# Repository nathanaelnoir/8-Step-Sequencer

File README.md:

<h1>ℤ₈ Modulo-8 Sequencer</h1>

Modulo-8 Sequencer is an 8-step Eurorack sequencer with an onboard clock, external clock/reset inputs, and separate clock, gate, and CV outputs.

## Contents

- Overview
- Features
- Build & assembly notes
- Testing
- License & contributing

## Overview

This repository contains the KiCad 9 design files for Modulo-8 Sequencer, a straightforward 8-step CV/gate sequencer for Eurorack. Eight pots set the step voltages, the LEDs show the current position, and the module can run from its own clock or from an external pulse. `CLOCK OUT`, `GATE OUT`, `CV OUT`, and `RESET` are all available on the front panel.

## Features

- 8-step sequencer built around `CD4017BE` and `TL074`.
- Internal clock plus external `CLOCK IN`.
- Separate `CLOCK OUT`, `GATE OUT`, `CV OUT`, and `RESET` jacks.
- Eight 100 k step pots for setting the sequence voltage.
- Eight step LEDs for visual feedback.
- Rotary switch wired across `Count0` to `Count7` for loop-length / step-count selection.
- Standard Eurorack power: `+12 V / -12 V / GND` on a 10-pin header.
- Mixed build: SMD passives, diodes, and transistors, with through-hole panel hardware.

## Build & assembly notes

- Check pin-1 orientation on `U1` (`TL074`) and `U3` (`CD4017BE`) before soldering.
- Double-check the Eurorack power header orientation before applying power. Getting that wrong is an easy way to ruin the build.
- Panel hardware is not minimal: five 3.5 mm jacks, eight step pots, eight LEDs, several toggle switches, one rotary switch, and two trimmers (`RV1`, `RV2`).
- The power section includes ferrite beads and local decoupling on the rails. Populate it exactly as shown.
- This is a mixed SMD + THT build, so it makes sense to solder the low-profile SMD parts first and leave the panel hardware for last.

## Testing

1. Power the module from a current-limited Eurorack supply and verify `+12 V`, `-12 V`, and `GND` at the header and test points before patching anything.
2. Let the internal clock run and check that the step LEDs advance in order and that `CLOCK OUT` is pulsing.
3. Feed a known clock into `CLOCK IN` and confirm the sequence advances cleanly from the external source.
4. Trigger `RESET` and make sure the sequencer returns to step 1 or to the selected loop point.
5. Watch `GATE OUT` and `CV OUT` on a scope or with downstream modules and confirm that the outputs follow the programmed steps.

## License & contributing

No `LICENSE` file has been added to this repository yet. Until that changes, assume the design is shared for reference, not under an explicit open-source license.

If a license is added later, this section can be updated properly.

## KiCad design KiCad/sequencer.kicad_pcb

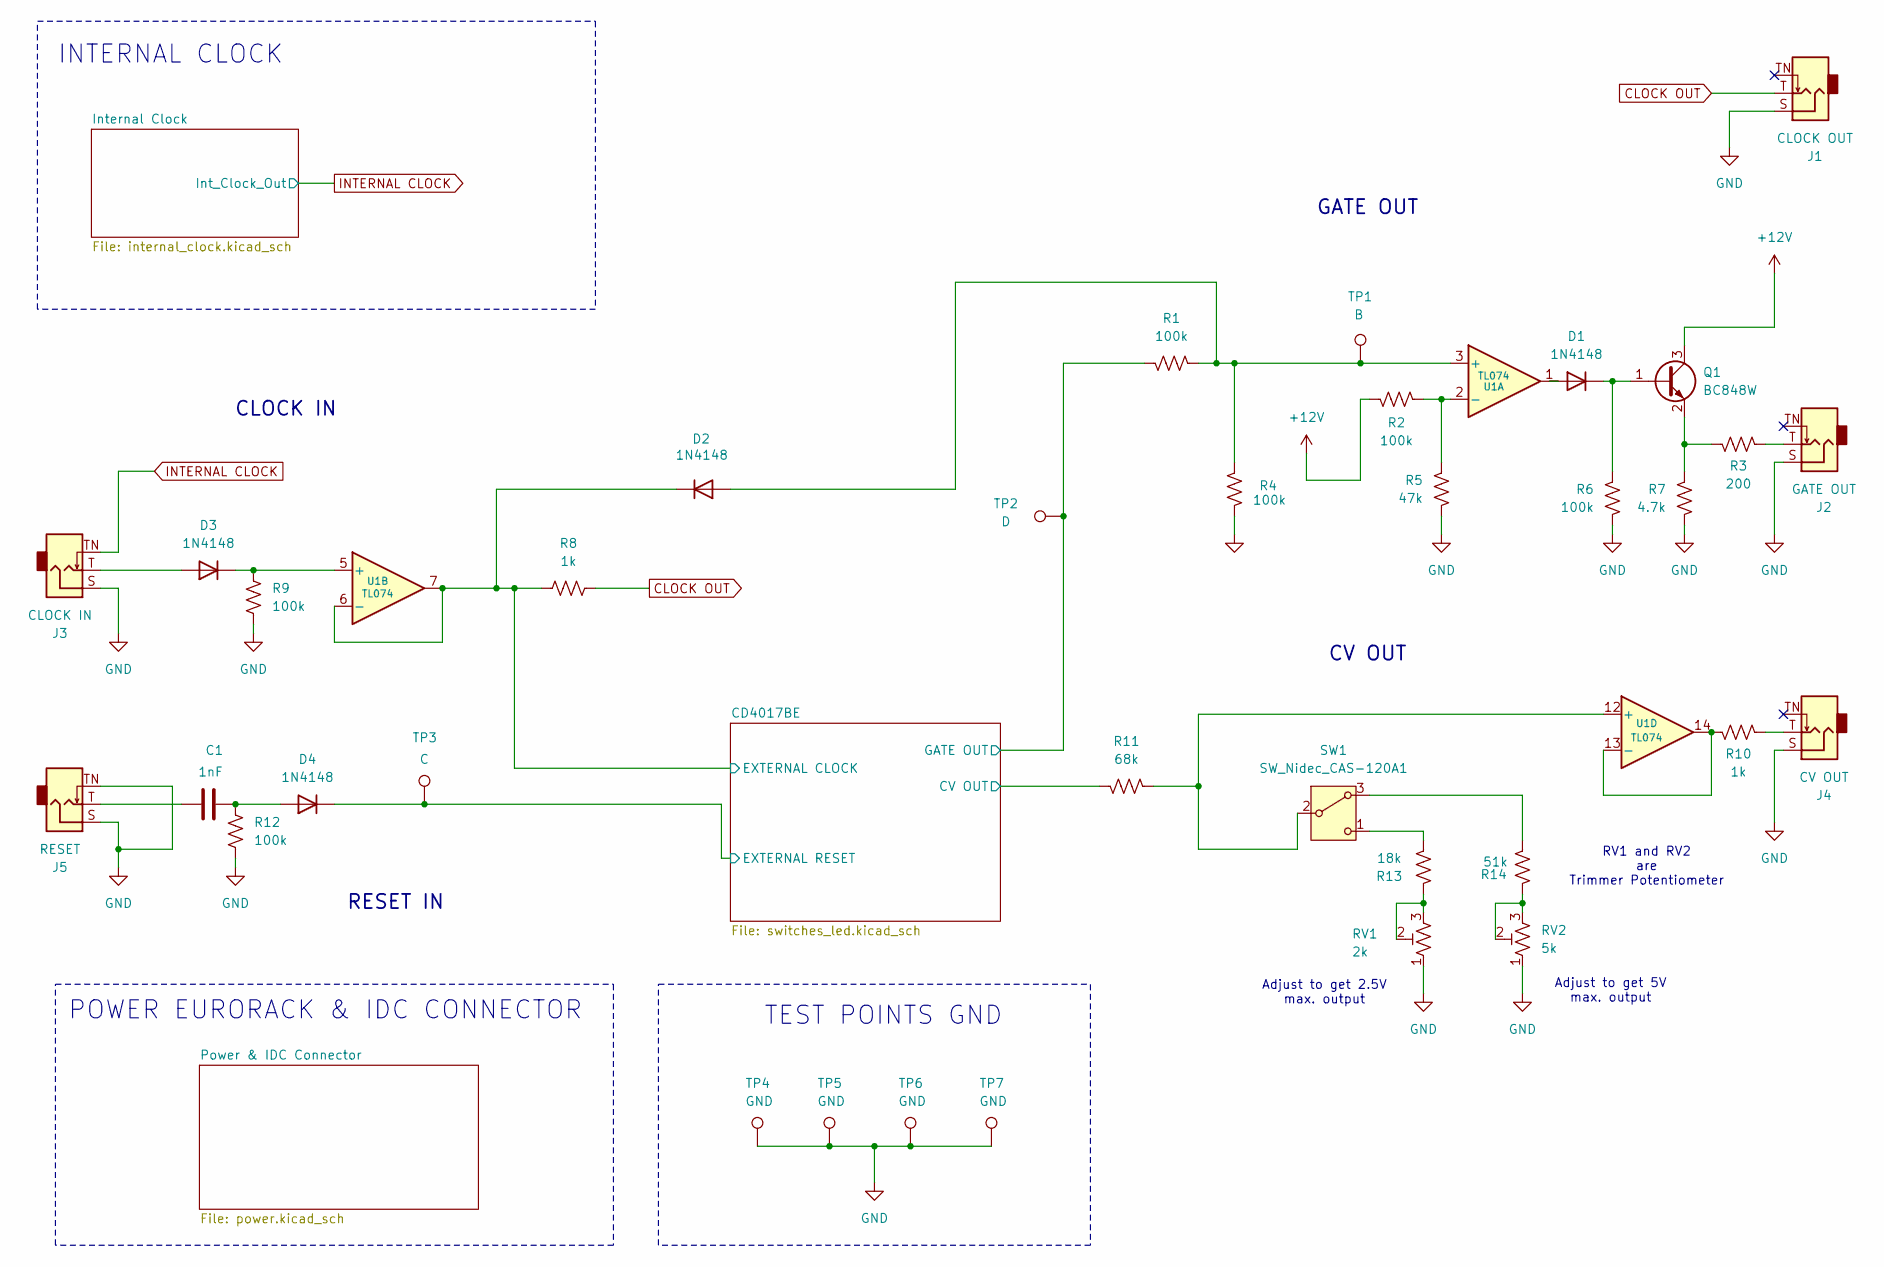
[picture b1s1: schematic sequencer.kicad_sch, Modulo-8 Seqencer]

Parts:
C1: 1nF; C_0805_2012Metric_Pad1.18x1.45mm_HandSolder
D1, D2, D3, D4: 1N4148; D_SOD-323_HandSoldering
J1: CLOCK OUT; Jack_3.5mm_QingPu_WQP-PJ398SM_Vertical
J2: GATE OUT; Jack_3.5mm_QingPu_WQP-PJ398SM_Vertical
J3: CLOCK IN; Jack_3.5mm_QingPu_WQP-PJ398SM_Vertical
J4: CV OUT; Jack_3.5mm_QingPu_WQP-PJ398SM_Vertical
J5: RESET; Jack_3.5mm_QingPu_WQP-PJ398SM_Vertical
Q1: BC848W; SOT-323_SC-70
R1, R2, R4, R6, R9, R12: 100k; R_0805_2012Metric_Pad1.20x1.40mm_HandSolder
R3: 200; R_0805_2012Metric_Pad1.20x1.40mm_HandSolder
R5: 47k; R_0805_2012Metric_Pad1.20x1.40mm_HandSolder
R7: 4.7k; R_0805_2012Metric_Pad1.20x1.40mm_HandSolder
R8, R10: 1k; R_0805_2012Metric_Pad1.20x1.40mm_HandSolder
R11: 68k; R_0805_2012Metric_Pad1.20x1.40mm_HandSolder
R13: 18k; R_0805_2012Metric_Pad1.20x1.40mm_HandSolder
R14: 51k; R_0805_2012Metric_Pad1.20x1.40mm_HandSolder
RV1: 2k; Trimmer_Bourns_3296W_50k_THT
RV2: 5k; Trimmer_Bourns_3296W_50k_THT
SW1: SW_Nidec_CAS-120A1; Switch_Toggle_Dailywell_MS1T1B1M2QES_SPDT
TP1: B; TestPoint_Pad_D1.5mm
TP2: D; TestPoint_Pad_D1.5mm
TP3: C; TestPoint_Pad_D1.5mm
TP4, TP5, TP6, TP7: GND; TestPoint_Pad_D1.5mm
U1: TL074; SOIC-14_3.9x8.7mm_P1.27mm

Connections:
+12V: Q1.3 (C), R2.1; also elsewhere on the board
/CD4017BE/CV OUT: R11.1; also elsewhere on the board
/CD4017BE/EXTERNAL CLOCK: D2.1 (K), R8.2, U1.6 (-), U1.7; also elsewhere on the board
/CD4017BE/EXTERNAL RESET: D4.1 (K), TP3.1; also elsewhere on the board
/CD4017BE/GATE OUT: R1.1, TP2.1; also elsewhere on the board
CLOCK OUT: J1.T, R8.1
GND: J1.S, J2.S, J3.S, J4.S, J5.S, J5.TN, R4.1, R5.1, R6.1, R7.1, R9.1, R12.1, RV1.1, RV2.1, TP4.1, TP5.1, TP6.1, TP7.1; also elsewhere on the board
INTERNAL CLOCK: J3.TN; also elsewhere on the board
unnamed: C1.2, J5.T
unnamed: D1.2 (A), U1.1
unnamed: D1.1 (K), Q1.1 (B), R6.2
unnamed: D2.2 (A), R1.2, R4.2, TP1.1, U1.3 (+)
unnamed: D3.2 (A), J3.T
unnamed: D3.1 (K), R9.2, U1.5 (+)
unnamed: C1.1, D4.2 (A), R12.2
unnamed: J2.T, R3.1
unnamed: J4.T, R10.1
unnamed: Q1.2 (E), R3.2, R7.2
unnamed: R13.1, RV1.2, RV1.3
unnamed: R14.1, RV2.2, RV2.3
unnamed: R14.2, SW1.3 (A)
unnamed: R11.2, SW1.2 (B), U1.12 (+)
unnamed: R13.2, SW1.1 (C)
unnamed: R2.2, R5.2, U1.2 (-)
unnamed: R10.2, U1.13 (-), U1.14

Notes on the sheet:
POWER EURORACK & IDC CONNECTOR
Adjust to get 2.5V max. output
RV1 and RV2 are Trimmer Potentiometer
TEST POINTS GND
INTERNAL CLOCK
Adjust to get 5V max. output
CV OUT
GATE OUT
RESET IN
CLOCK IN

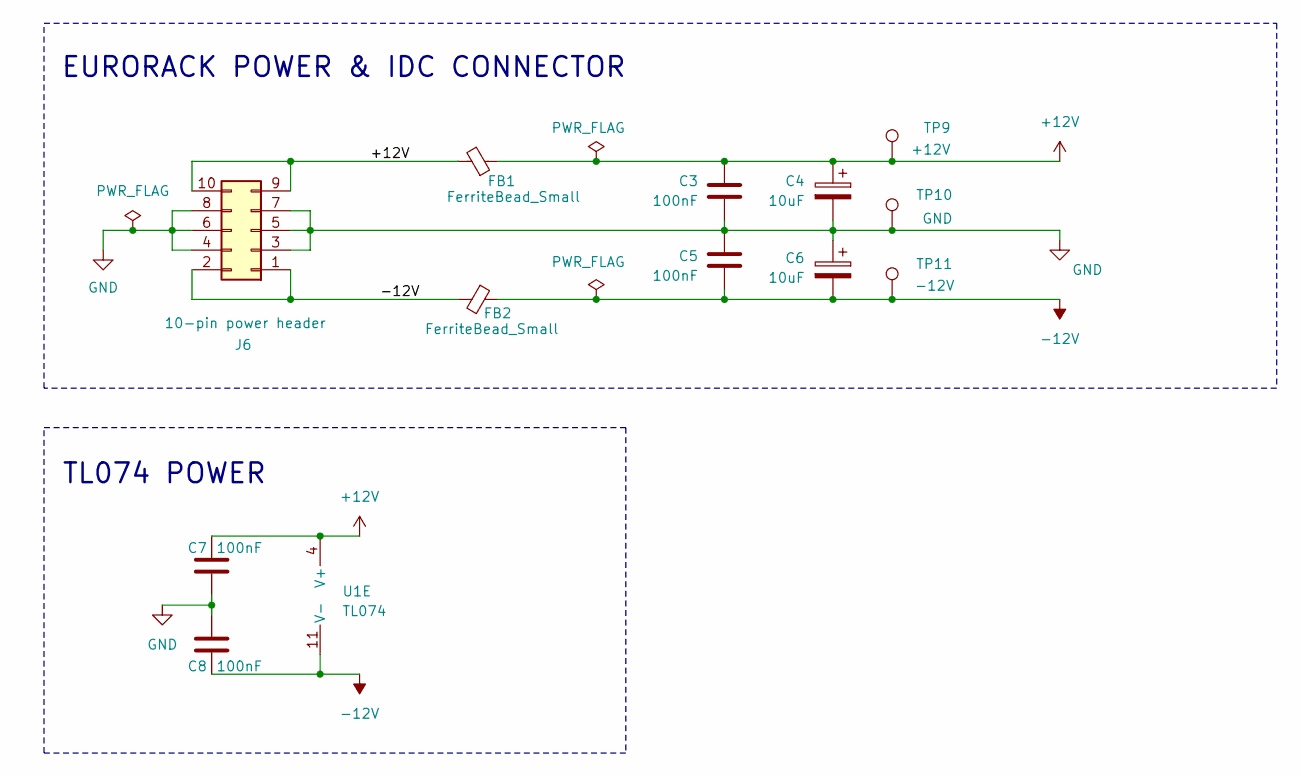
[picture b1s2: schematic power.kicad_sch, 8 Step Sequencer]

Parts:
C3, C5, C7, C8: 100nF; C_0805_2012Metric_Pad1.18x1.45mm_HandSolder
C4, C6: 10uF; CP_Elec_5x5.4
FB1, FB2: FerriteBead_Small; L_0805_2012Metric_Pad1.05x1.20mm_HandSolder
J6: 10-pin power header; IDC-Header_2x05_P2.54mm_Vertical
TP9: +12V; TestPoint_Pad_D1.5mm
TP10: GND; TestPoint_Pad_D1.5mm
TP11: -12V; TestPoint_Pad_D1.5mm
U1: TL074; SOIC-14_3.9x8.7mm_P1.27mm

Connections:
+12V: C3.1, C4.1, C7.1, FB1.1, FB1.2, J6.9, J6.10, TP9.1, U1.4 (V+); also elsewhere on the board
-12V: C5.2, C6.2, C8.2, FB2.1, FB2.2, J6.1, J6.2, TP11.1, U1.11 (V-)
GND: C3.2, C4.2, C5.1, C6.1, C7.2, C8.1, J6.3, J6.4, J6.5, J6.6, J6.7, J6.8, TP10.1; also elsewhere on the board

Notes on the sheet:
TL074 POWER
EURORACK POWER & IDC CONNECTOR

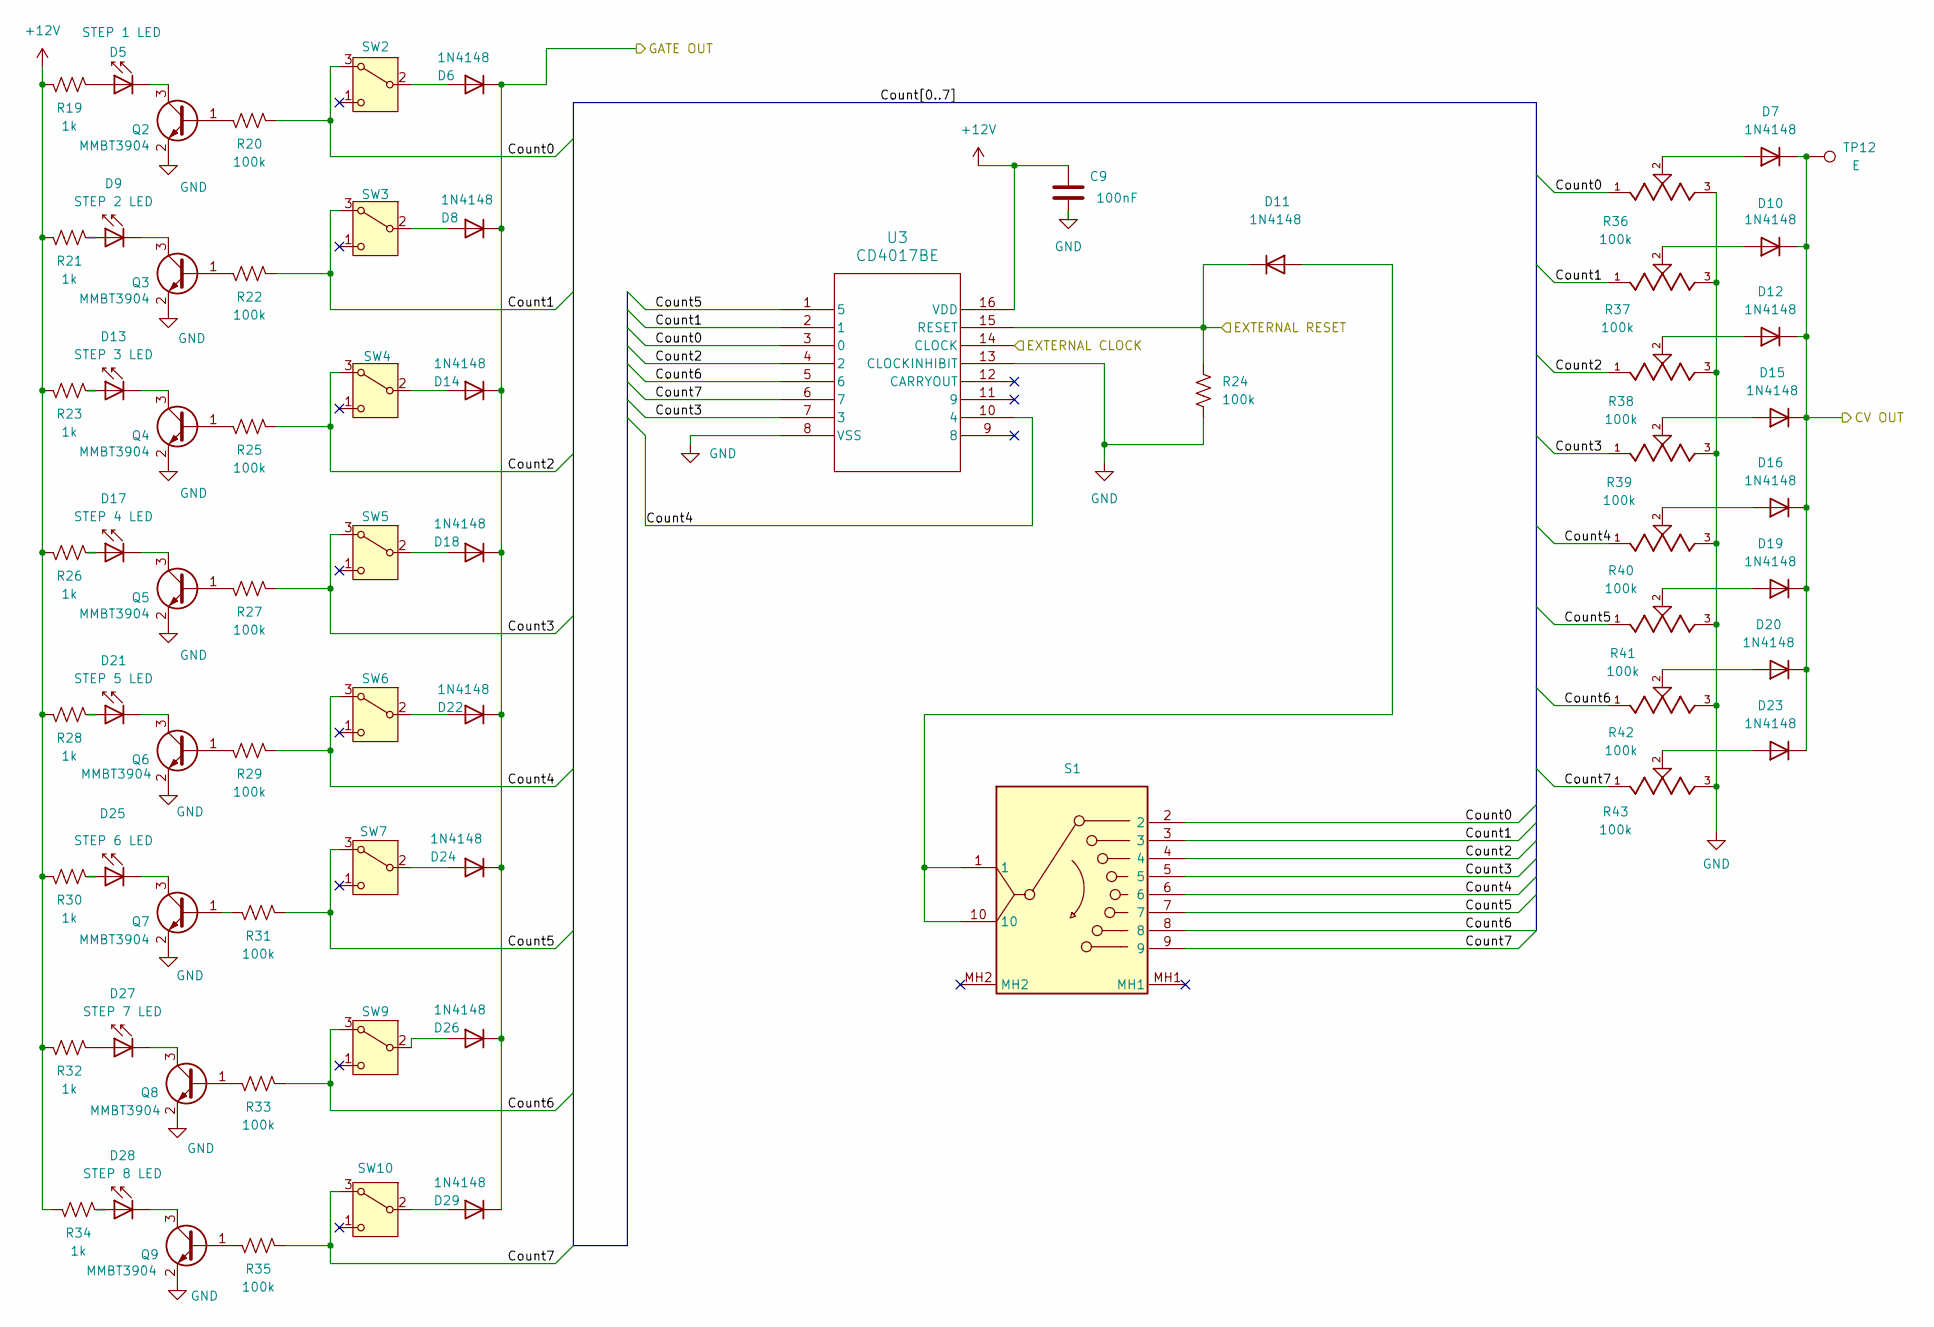
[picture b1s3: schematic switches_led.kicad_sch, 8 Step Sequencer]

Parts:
C9: 100nF; C_0805_2012Metric_Pad1.18x1.45mm_HandSolder
D5: STEP 1 LED; LED_D3.0mm_Clear
D6, D7, D8, D10, D11, D12, D14, D15, D16, D18, D19, D20, D22, D23, D24, D26, D29: 1N4148; D_SOD-323_HandSoldering
D9: STEP 2 LED; LED_D3.0mm_Clear
D13: STEP 3 LED; LED_D3.0mm_Clear
D17: STEP 4 LED; LED_D3.0mm_Clear
D21: STEP 5 LED; LED_D3.0mm_Clear
D25: STEP 6 LED; LED_D3.0mm_Clear
D27: STEP 7 LED; LED_D3.0mm_Clear
D28: STEP 8 LED; LED_D3.0mm_Clear
Q2, Q3, Q4, Q5, Q6, Q7, Q8, Q9: MMBT3904; SOT-23
R19, R21, R23, R26, R28, R30, R32, R34: 1k; R_0805_2012Metric_Pad1.20x1.40mm_HandSolder
R20, R22, R24, R25, R27, R29, R31, R33, R35: 100k; R_0805_2012Metric_Pad1.20x1.40mm_HandSolder
R36, R37, R38, R39, R40, R41, R42, R43: 100k; Potentiometer_Alpha_RD901F_Vertical_Alt
S1: Switch_Rotary_Alpha_SR1712F_1P8T; Mouser Part Number 105-SR1712F-18NS
SW2, SW3, SW4, SW5, SW6, SW7, SW9, SW10: Switch_Toggle_Dailywell_MS1T1B1M2QES_SPDT
TP12: E; TestPoint_Pad_D1.5mm
U3: CD4017BE; IC_DIP-16_CD4017BE_THT

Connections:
+12V: C9.1, R19.1, R21.1, R23.1, R26.1, R28.1, R30.1, R32.1, R34.1, U3.16 (VDD); also elsewhere on the board
/CD4017BE/CV OUT: D7.1 (K), D10.1 (K), D12.1 (K), D15.1 (K), D16.1 (K), D19.1 (K), D20.1 (K), D23.1 (K), TP12.1; also elsewhere on the board
/CD4017BE/Count0: R20.2, R36.1, S1.2, SW2.3 (A), U3.3 (0)
/CD4017BE/Count1: R22.2, R37.1, S1.3, SW3.3 (A), U3.2 (1)
/CD4017BE/Count2: R25.2, R38.1, S1.4, SW4.3 (A), U3.4 (2)
/CD4017BE/Count3: R27.2, R39.1, S1.5, SW5.3 (A), U3.7 (3)
/CD4017BE/Count4: R29.2, R40.1, S1.6, SW6.3 (A), U3.10 (4)
/CD4017BE/Count5: R31.2, R41.1, S1.7, SW7.3 (A), U3.1 (5)
/CD4017BE/Count6: R33.2, R42.1, S1.8, SW9.3 (A), U3.5 (6)
/CD4017BE/Count7: R35.2, R43.1, S1.9, SW10.3 (A), U3.6 (7)
/CD4017BE/EXTERNAL CLOCK: U3.14 (CLOCK); also elsewhere on the board
/CD4017BE/EXTERNAL RESET: D11.1 (K), R24.2, U3.15 (RESET); also elsewhere on the board
/CD4017BE/GATE OUT: D6.1 (K), D8.1 (K), D14.1 (K), D18.1 (K), D22.1 (K), D24.1 (K), D26.1 (K), D29.1 (K); also elsewhere on the board
GND: C9.2, Q2.2 (E), Q3.2 (E), Q4.2 (E), Q5.2 (E), Q6.2 (E), Q7.2 (E), Q8.2 (E), Q9.2 (E), R24.1, R36.3, R37.3, R38.3, R39.3, R40.3, R41.3, R42.3, R43.3, U3.8 (VSS), U3.13 (CLOCKINHIBIT); also elsewhere on the board
unnamed: D5.2 (A), R19.2
unnamed: D5.1 (K), Q2.3 (C)
unnamed: D6.2 (A), SW2.2 (B)
unnamed: D7.2 (A), R36.2
unnamed: D8.2 (A), SW3.2 (B)
unnamed: D9.2 (A), R21.2
unnamed: D9.1 (K), Q3.3 (C)
unnamed: D10.2 (A), R37.2
unnamed: D11.2 (A), S1.1, S1.10
unnamed: D12.2 (A), R38.2
unnamed: D13.2 (A), R23.2
unnamed: D13.1 (K), Q4.3 (C)
unnamed: D14.2 (A), SW4.2 (B)
unnamed: D15.2 (A), R39.2
unnamed: D16.2 (A), R40.2
unnamed: D17.2 (A), R26.2
unnamed: D17.1 (K), Q5.3 (C)
unnamed: D18.2 (A), SW5.2 (B)
unnamed: D19.2 (A), R41.2
unnamed: D20.2 (A), R42.2
unnamed: D21.2 (A), R28.2
unnamed: D21.1 (K), Q6.3 (C)
unnamed: D22.2 (A), SW6.2 (B)
unnamed: D23.2 (A), R43.2
unnamed: D24.2 (A), SW7.2 (B)
unnamed: D25.2 (A), R30.2
unnamed: D25.1 (K), Q7.3 (C)
unnamed: D26.2 (A), SW9.2 (B)
unnamed: D27.2 (A), R32.2
unnamed: D27.1 (K), Q8.3 (C)
unnamed: D28.2 (A), R34.2
unnamed: D28.1 (K), Q9.3 (C)
unnamed: D29.2 (A), SW10.2 (B)
unnamed: Q2.1 (B), R20.1
unnamed: Q3.1 (B), R22.1
unnamed: Q4.1 (B), R25.1
unnamed: Q5.1 (B), R27.1
unnamed: Q6.1 (B), R29.1
unnamed: Q7.1 (B), R31.1
unnamed: Q8.1 (B), R33.1
unnamed: Q9.1 (B), R35.1

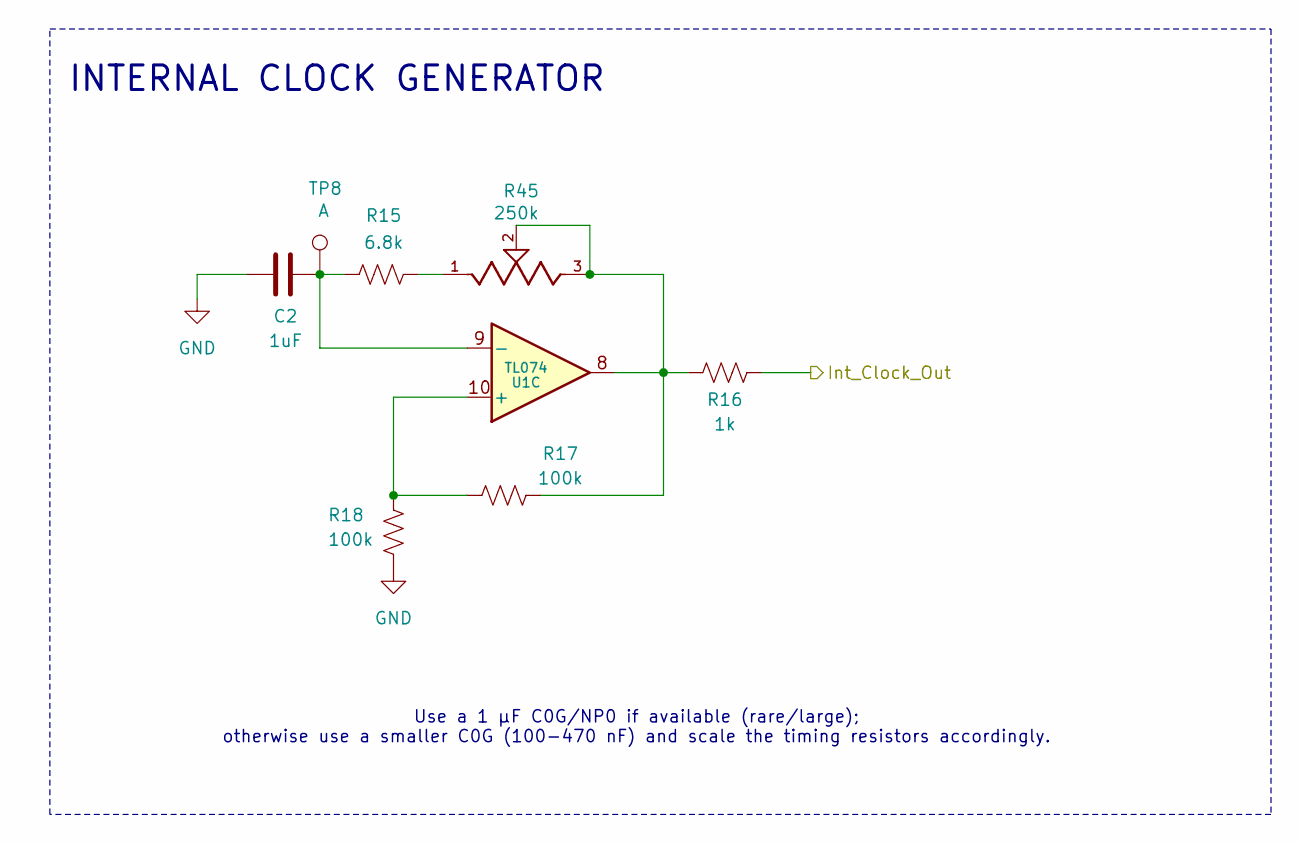
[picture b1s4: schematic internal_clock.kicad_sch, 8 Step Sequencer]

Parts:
C2: 1uF; Capacitor_Film_KEMET_R82DC4100AA60J_THT
R15: 6.8k; R_0805_2012Metric_Pad1.20x1.40mm_HandSolder
R16: 1k; R_0805_2012Metric_Pad1.20x1.40mm_HandSolder
R17, R18: 100k; R_0805_2012Metric_Pad1.20x1.40mm_HandSolder
R45: 250k; Potentiometer_Alpha_RD901F_Vertical_Alt
TP8: A; TestPoint_Pad_D1.5mm
U1: TL074; SOIC-14_3.9x8.7mm_P1.27mm

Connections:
GND: C2.1, R18.1; also elsewhere on the board
INTERNAL CLOCK: R16.1; also elsewhere on the board
unnamed: R15.1, R45.1
unnamed: R16.2, R17.1, R45.2, R45.3, U1.8
unnamed: R17.2, R18.2, U1.10 (+)
unnamed: C2.2, R15.2, TP8.1, U1.9 (-)

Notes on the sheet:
INTERNAL CLOCK GENERATOR
Use a 1 µF C0G/NP0 if available (rare/large); otherwise use a smaller C0G (100-470 nF) and scale the timing resistors accordingly.

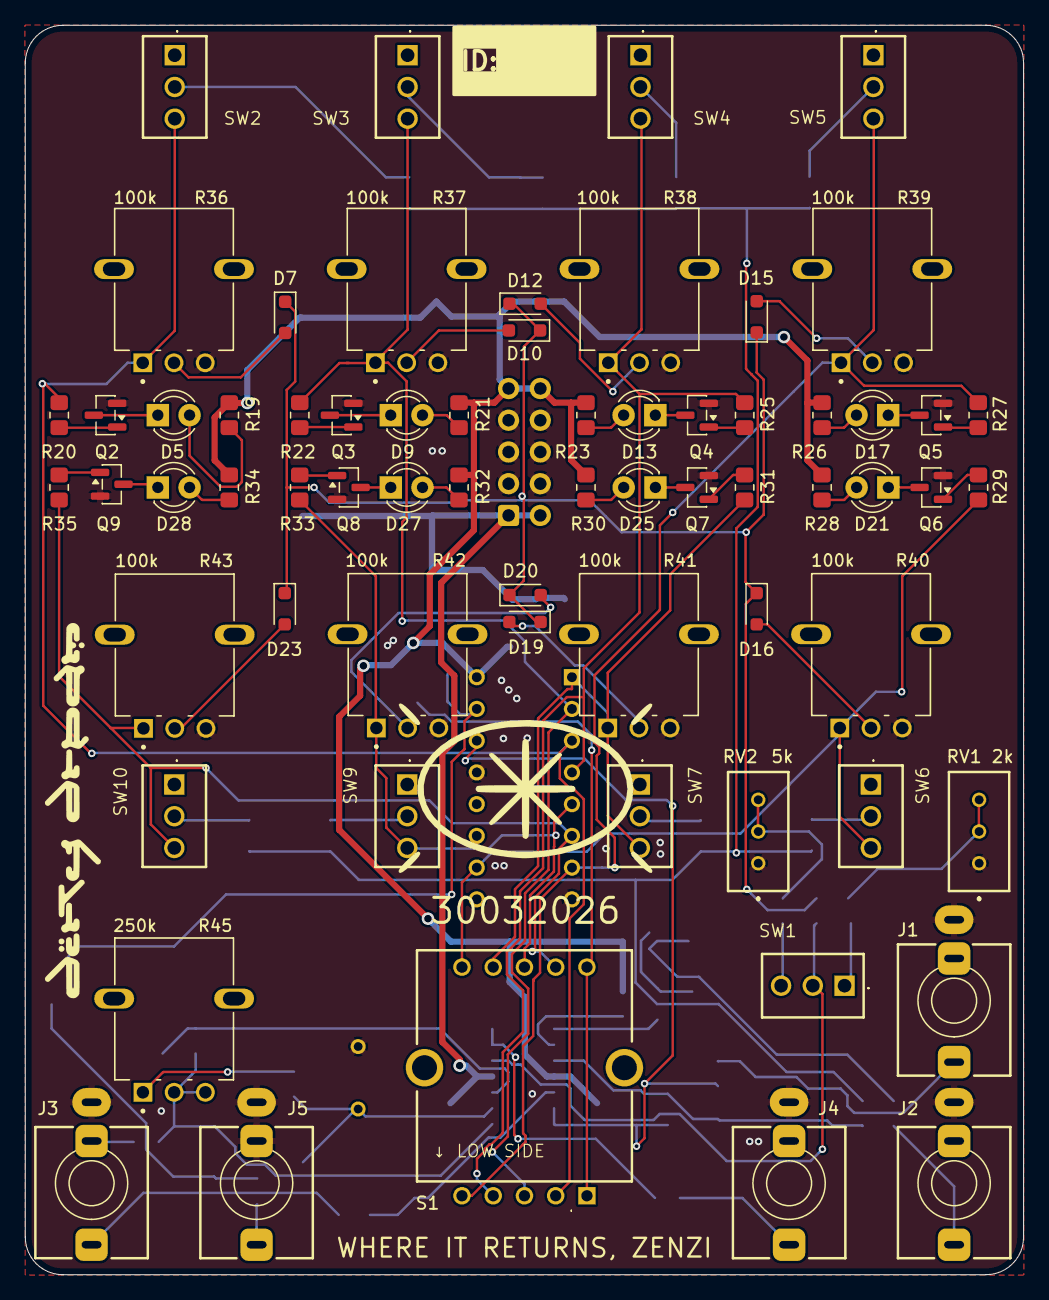
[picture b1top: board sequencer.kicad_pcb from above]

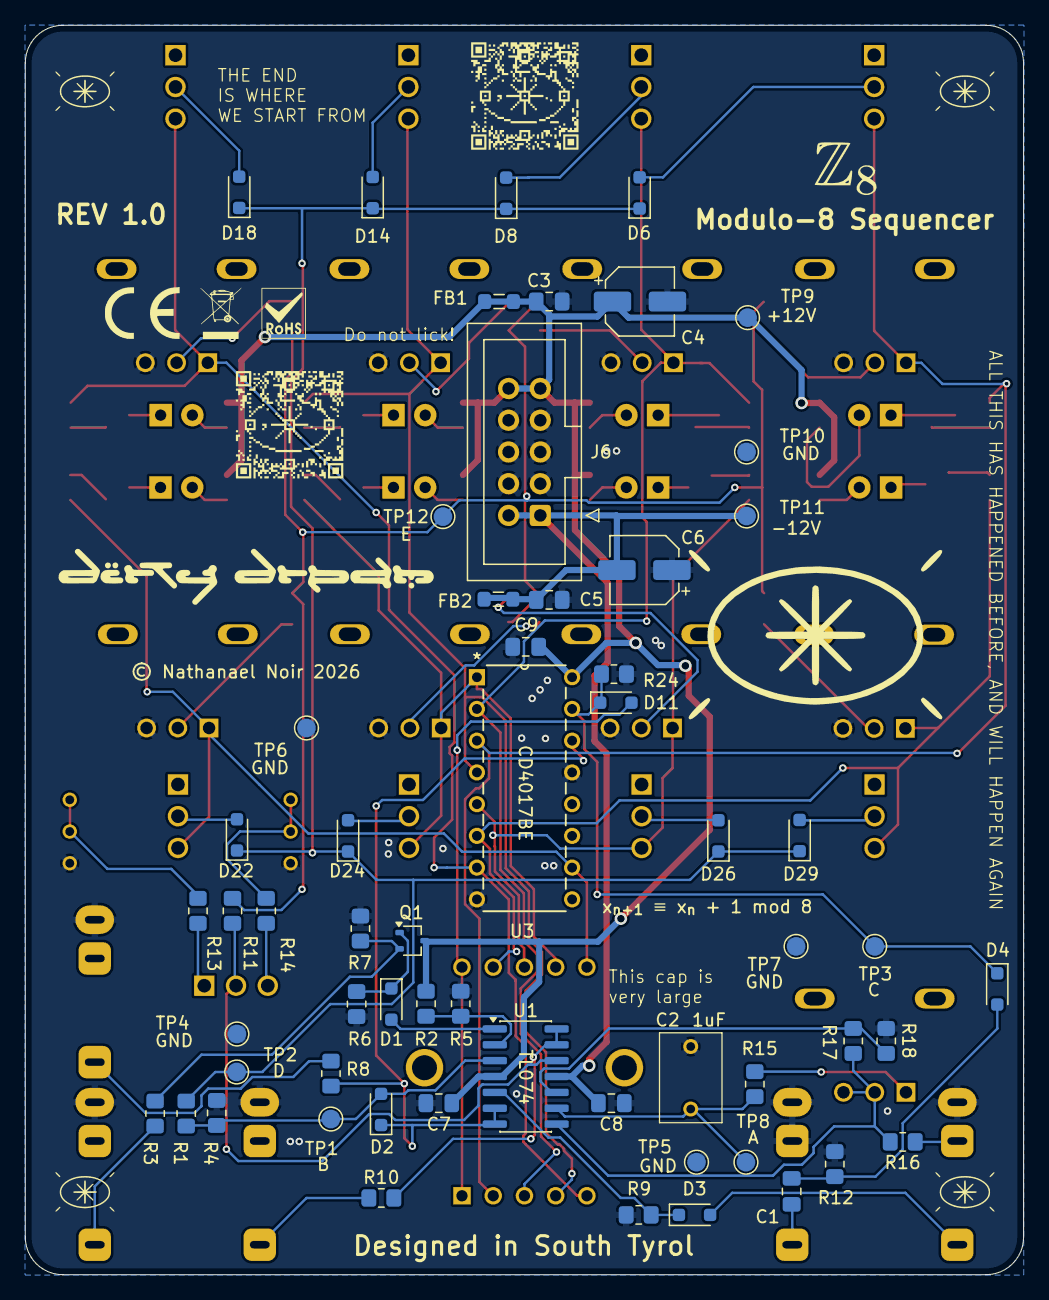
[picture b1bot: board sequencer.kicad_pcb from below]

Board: 2 copper layers, 79.9 x 100.0 mm, 125 parts (59 on the bottom side), 79 nets.

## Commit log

2026-03-09 schematic: update cicada schematic
2026-03-10 refactor(kicad): move switch/LED driver logic into switches_led sheet
2026-03-10 refactor(kicad): finishing root
2026-03-10 refactor(kicad): first ERC run
2026-03-13 Refine KiCad schematics for power, test points, and control values
    - replace schematic +12V/-12V global labels with proper power symbols
    - add GND test points and reorganize the power/IDC and main sequencer
    sheets
    - retune sequencer values including R33/R34 to 51k, R35 to 68k, C8 to
    1nF, and trim pots to 2k/5k
    - update switch/LED sheet labels and pot values, renaming LEDs by step
2026-03-13 Updated sheet names
2026-03-13 Updating sheet names
2026-03-14 adding missing footprints to the power supply
2026-03-15 adding missing SMD footprints
2026-03-15 adding Test Point D
2026-03-16 adding footprints
2026-03-18 adding footprint for rotary switch P1S8
2026-03-19 adding new rotary switch
2026-03-19 initiating pcb layout
2026-03-21 placing layout frontview
2026-03-21 fixing some errors in schematics; first component placement
2026-03-22 connecting all components and adding copper layers, vias tracks…
2026-03-23 rerouting and editing silkscreen
2026-03-24 re-placing components; optimizing text on silkscreen
2026-03-25 changing position on silkscreen
2026-03-25 fixing drc errors; mirroring potentiometers in sch due to error; mirroring switches on pcb
    to do: change symbol description potentiometer (cw, ccw)
2026-03-27 placing logos
2026-03-27 finalizing silkscreen
2026-03-27 adding a README.md
2026-03-29 adding qr code
2026-03-30 Refine README wording for Modulo-8 Sequencer
2026-04-02 new logo, via correction, gerber
2026-04-02 changing folder name
2026-04-02 changing file names

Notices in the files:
Electronics/internal_clock.kicad_sch:
© Dirty Dream - Nathanael Noir
KiCad/sequencer.kicad_pcb:
© Nathanael Noir 2026
README.md:
License: TBD
